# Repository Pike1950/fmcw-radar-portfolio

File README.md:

# 24 GHz FMCW Radar Sensor

A personal engineering portfolio project: a short-range 24 GHz FMCW radar sensor spanning an RF front end, a mixed-signal I/Q baseband, and an FPGA digital backend. It began as a baseband redesign of a Texas Tech senior capstone (HOTRODS, Spring 2020) and has grown into a complete radar sensor design, carried out with the discipline of 4+ years of hardware validation at Texas Instruments.

## Project Overview

This project demonstrates RF integration, mixed-signal PCB design, digital hardware design, hardware verification, and system-level engineering, with first-principles documentation explaining every design decision. The completed work is a corrected, first-principles baseband design and its system design document; the active phase is scaling that foundation into a full 24 GHz radar sensor.

## The System

An FMCW (Frequency-Modulated Continuous Wave) radar transmits a frequency chirp, receives the reflection from a target, and mixes it with the current transmit frequency to produce a low-frequency beat signal. The beat frequency is proportional to range; the chirp-to-chirp phase gives Doppler velocity, and a complex (I/Q) baseband resolves the sign of that velocity (approaching versus receding).

The sensor is built around an integrated 24 GHz transceiver MMIC and is partitioned into two boards plus a downstream digital backend:

```
RF FRONT-END MODULE                       I/Q BASEBAND BOARD                    DIGITAL BACKEND
BGT24MTR11 (24 GHz, 1 TX / 1 RX)          per channel:                          range-Doppler FFT
 on-chip VCO, PA, LNA, I/Q mixers   I,Q   VGA -> anti-alias -> 18-bit SAR ADC    (FPGA / MCU) -> host
 TX/RX antennas, chirp ramp,        --->  I and Q sampled simultaneously
 first gain stage                  (zero  SPI control of the MMIC
                                     IF)
```

The two boards meet at a low-frequency analog I/Q interface, not a 24 GHz one, because the MMIC downconverts on-chip. That seam is what makes the split practical: the costly, iteration-prone 24 GHz RF and antennas stay on a small module, while the baseband stays on inexpensive FR4 and can be brought up and validated on its own.

## Evolution: Rev A to Rev B to Rev C

- **Rev A (2020).** 5.8 GHz, 3 RX channels, 182 components, Eagle, a single flat sheet. Built as the Texas Tech senior capstone; non-functional. The headline defect was a 10 kHz chirp rate that produced only about 5 ADC samples per ramp, far too few for FFT range extraction.
- **Rev B (current).** Began as a scaled, corrected 5.8 GHz baseband (one channel, KiCad 9, a modern signal chain, DFT-first methodology), captured as schematic plus a first-principles system design document. Rather than fabricate that band, Rev B is now redefined as the **24 GHz I/Q radar**: the band moves to 24 GHz, the project adopts the BGT24MTR11 (so it now owns the RF front end, not just the baseband), the baseband goes complex I/Q, and the sensor splits into an RF module and a baseband board. The baseband modernization below carries forward intact.
- **Rev C.** Additional receive channels for angle estimation, the original trilateration goal, on a proven single-channel Rev B.

### Baseband modernization (carried forward from the 5.8 GHz Rev B)

These corrections to the capstone baseband are band-agnostic and carry directly into the 24 GHz I/Q design.

| Aspect | Rev A (2020) | Rev B baseband (carried forward) |
| --- | --- | --- |
| EDA | Eagle 9.5, flat single sheet | KiCad 9, hierarchical |
| VGA | LT6230 + MCP4017 I²C digital pot | PGA113 (SPI, internal gain resistors) |
| ADC | ADS1174 (16-bit, 64-pin QFP, solder bridges) | ADS8881 (18-bit, 10-pin VSSOP) |
| SE to Diff | LTC6242 (improvised, no VOCM) | THS4531A (true FDA with VOCM) |
| Power | Single 3.3 V rail | 3V3A / 3V3D split via ferrite bead |
| Reference | Resistor divider | REF5025 (2.500 V, 0.05%, 3 µVpp) |
| DFT | None | J_DFT header, 17 TPs, 5 MMCX, 6 isolation resistors |

On top of this, the 24 GHz move adds an integrated-MMIC RF front end, a complex I/Q baseband (the chain above duplicated for I and Q with simultaneous sampling), and the two-board partition.

## Key Documents

| Document | Description |
| --- | --- |
| [System Design Document](https://pike1950.github.io/fmcw-radar-portfolio/docs/system-design/System_Design_Document_RevB.html) | The 24 GHz radar system SDD, restyled to the PMVB module-doc schema with PHYSICS / DECISION / TRADEOFF / RISK reasoning callouts. Covers the two-board architecture, the carry-over analog design (power, references, gain, anti-alias filter, DFT), the FMCW principles, and an open decision register tracking the remaining 24 GHz choices. |

## Technical Highlights

### Analog and mixed-signal design

- **Supply splitting via ferrite bead.** BLM18PG221SN1D (220 Ω at 100 MHz) isolates analog from digital supply noise on a single continuous ground plane, with first-principles impedance analysis.
- **Paired decoupling capacitors.** Matched cap pairs (for example 10 µF + 100 nF) with different self-resonant frequencies for low impedance across a wide band, placed per a derived trace-inductance budget.
- **DFT-first methodology.** Test points, MMCX probes, and isolation resistors designed before the signal chain, now applied per channel for I and Q.

### System-level analysis

- **Chirp-rate correction.** Identified the Rev A parameter mismatch (about 5 samples per ramp) and derived the corrected chirp plan from first principles (sample-count-per-ramp to FFT resolution). The analysis is carrier-independent and re-derives the 24 GHz filter and ADC plan.
- **Band move to 24 GHz with complex I/Q.** Moving from 5.8 GHz to the 24 GHz ISM band raises range resolution from about 5 m to about 0.6 m and brings the RF front end into scope through an integrated MMIC. Complex I/Q sampling adds sign-of-velocity discrimination.
- **Designed for validation.** The board is designed for standalone bring-up and characterization on a homebrew SCPI instrument platform (see Related Repositories).

### Digital backend (planned)

SystemVerilog modules targeting the Gowin GW5A (Tang Primer 25K): SPI masters for the ADS8881 and the MMIC, a chirp ramp / DDS generator, a configurable FIR, and a deterministic timing controller, all verified with self-checking Verilator testbenches. See `digital/spi-controller/`.

## Related Repositories

| Repository | Description | Status |
| --- | --- | --- |
| [32-bit RISC Pipelined Processor](https://github.com/Pike1950/BradW_ECE4375_RISC_Pipeline) | 4-stage pipelined CPU refactored from Verilog to SystemVerilog. Shares the Verilator-clean SystemVerilog methodology used for this radar's digital backend. | SV conversion complete, synthesis next |
| [Poor Man's Validation Bench](https://github.com/Pike1950/poor-mans-validation-bench) | Modular SCPI + MCP instrument platform: Raspberry Pi 5 orchestration, Pico 2W USB-TMC modules, tiered FPGA. The bring-up and characterization platform for this radar. | Phase 0 complete; Module 1E (AWG) in build |

## Tools and Technologies

- **EDA:** KiCad 9. RF module on a controlled high-frequency stackup; baseband on FR4.
- **Simulation:** LTspice (analog), Verilator (digital), GTKWave (waveforms).
- **HDL:** SystemVerilog (digital backend, verification).
- **FPGA target:** Gowin GW5A (Sipeed Tang Primer 25K) for the digital backend.
- **Documentation:** Markdown rendered to HTML via Pandoc, PMVB-schema design docs with first-principles reasoning callouts.
- **Test automation:** PyVISA, integrating with the Poor Man's Validation Bench.

## Background

This project is one of four interconnected portfolio tracks:

1. **FMCW Radar Sensor** (this repo). RF integration plus mixed-signal PCB plus digital, with first-principles documentation and DFT-first methodology.
2. **Hardware Validation.** 4+ years at Texas Instruments (gate-driver characterization, automated test with LabVIEW / TestStand / PXI, DUT board design in Altium).
3. **Digital Design.** A pipelined RISC processor in SystemVerilog.
4. **Test Infrastructure.** The Poor Man's Validation Bench, a SCPI + MCP instrument platform.

The radar connects all four: a mixed-signal and RF sensor (track 1), designed with validation-engineer discipline (track 2), with an FPGA backend (track 3) characterized on the homebrew bench (track 4).

## Status

- **5.8 GHz baseband foundation (complete).** First-principles system design document and schematic capture of the corrected single-channel baseband. Established the methodology, the analog signal chain, and the DFT infrastructure that all carry forward.
- **24 GHz radar system design (in progress).**
  - System SDD reframed to the radar scope and the PMVB schema.
  - D1 resolved: BGT24MTR11 (1 TX / 1 RX), two-board partition (RF Front-End Module plus I/Q Baseband Board).
  - Open: antenna and RF stackup, ADC arrangement, ramp generation, chirp plan, and digital backend (tracked in the SDD decision register).
- **Next.** RF Front-End Module and I/Q Baseband Board schematics; digital backend RTL; bring-up and characterization on the Poor Man's Validation Bench.

## License

A personal engineering portfolio project. The FMCW radar originated as a Texas Tech senior capstone (HOTRODS, Spring 2020). The Rev B redesign, the 24 GHz radar system design, documentation, and all digital design work are by Bradley Ward.

## Contact

Bradley Ward, bradw858@gmail.com, [LinkedIn](https://linkedin.com/in/bradley-ward-49087766/)

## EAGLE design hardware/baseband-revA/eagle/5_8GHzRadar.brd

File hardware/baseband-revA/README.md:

# Baseband Rev A — Eagle 9.5 (Original Senior Capstone)

## Overview

Original 3-channel FMCW radar baseband designed for the HOTRODS senior capstone project at Texas Tech University (Spring 2020). This design is preserved for reference — it shows what was built originally and documents the failures that motivated the Rev B redesign.

## Architecture

- **3 identical RX channels**, each with: LT6230 VGA + MCP4017 I²C digital pot → 4th-order Sallen-Key LP (LTC6242, 25 kHz cutoff) → SE-to-Diff converter (LTC6242, remaining 2 amps)
- **On-board ADC:** ADS1174IPAPT (quad 16-bit, 52 kSPS, 64-pin TQFP)
- **Power:** NCP163ASN330T1G 3.3V LDO, single rail, no analog/digital splitting
- **182 total components** on a single flat Eagle sheet

## What Went Wrong

1. **ADS1174 solder bridges** — 64-pin QFP with sub-mm pitch; pins bridged during hand assembly
2. **TPS717185 (1.8V LDO) solder bridges** — same issue
3. **No test infrastructure** — zero test points, no DFT header, no isolation capability
4. **Power routing error** — power connected through RX_3 section only; RX_1 required wire jumpers
5. **COVID-19 shutdown** — prevented further debugging after initial partial success

## Files

- `5_8GHzRadar.sch` — Eagle 9.5 schematic (all 3 channels + power on one sheet)
- `5_8GHzRadar.brd` — Eagle 9.5 board layout (4-layer, OSHPark)

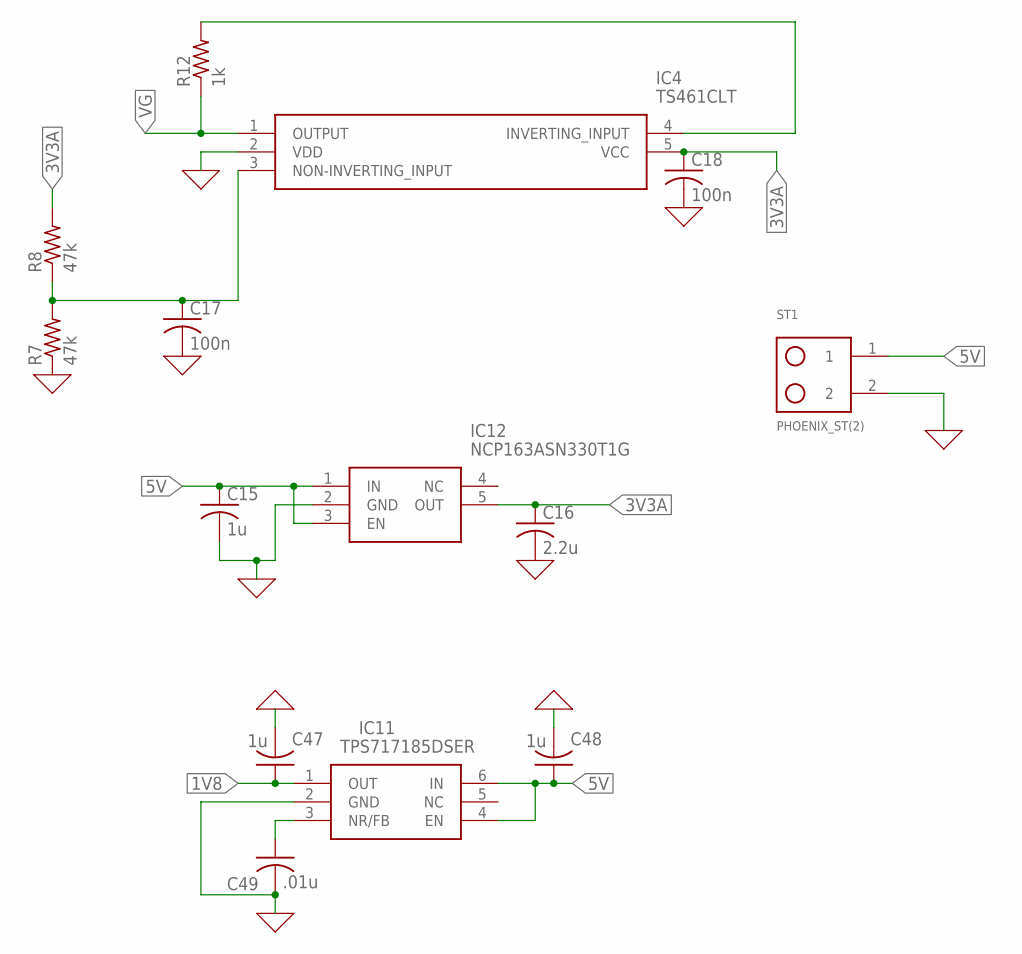
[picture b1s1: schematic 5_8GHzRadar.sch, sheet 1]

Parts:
C15, C47, C48: 1u; C0805
C16: 2.2u; C0805
C17, C18: 100n; C0805
C49: .01u; C0805
IC4: TS461CLT; SOT95P280X145-5N@1
IC11: TPS717185DSER; SON50P150X150X80-6N
IC12: NCP163ASN330T1G; SOT95P280X145-5N
R7, R8: 47k; R0805
R12: 1k; R0805
ST1: PHOENIX_ST(2); PHEONIX_SCREW(2)

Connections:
0: C15.2, C16.2, C17.2, C18.2, C47.2, C48.2, C49.2, IC4.2 (VDD), IC11.2 (GND), IC12.2 (GND), R7.1, ST1.2; also elsewhere on the board
1V8: C47.1, IC11.1 (OUT); also elsewhere on the board
3V3A: C16.1, C18.1, IC4.5 (VCC), IC12.5 (OUT), R8.2; also elsewhere on the board
5V: C15.1, C48.1, IC11.4 (EN), IC11.6 (IN), IC12.1 (IN), IC12.3 (EN), ST1.1; also elsewhere on the board
unnamed: C17.1, IC4.3 (NON-INVERTING_INPUT), R7.2, R8.1
unnamed: IC4.4 (INVERTING_INPUT), R12.2
unnamed: C49.1, IC11.3 (NR/FB)
VG: IC4.1 (OUTPUT), R12.1; also elsewhere on the board

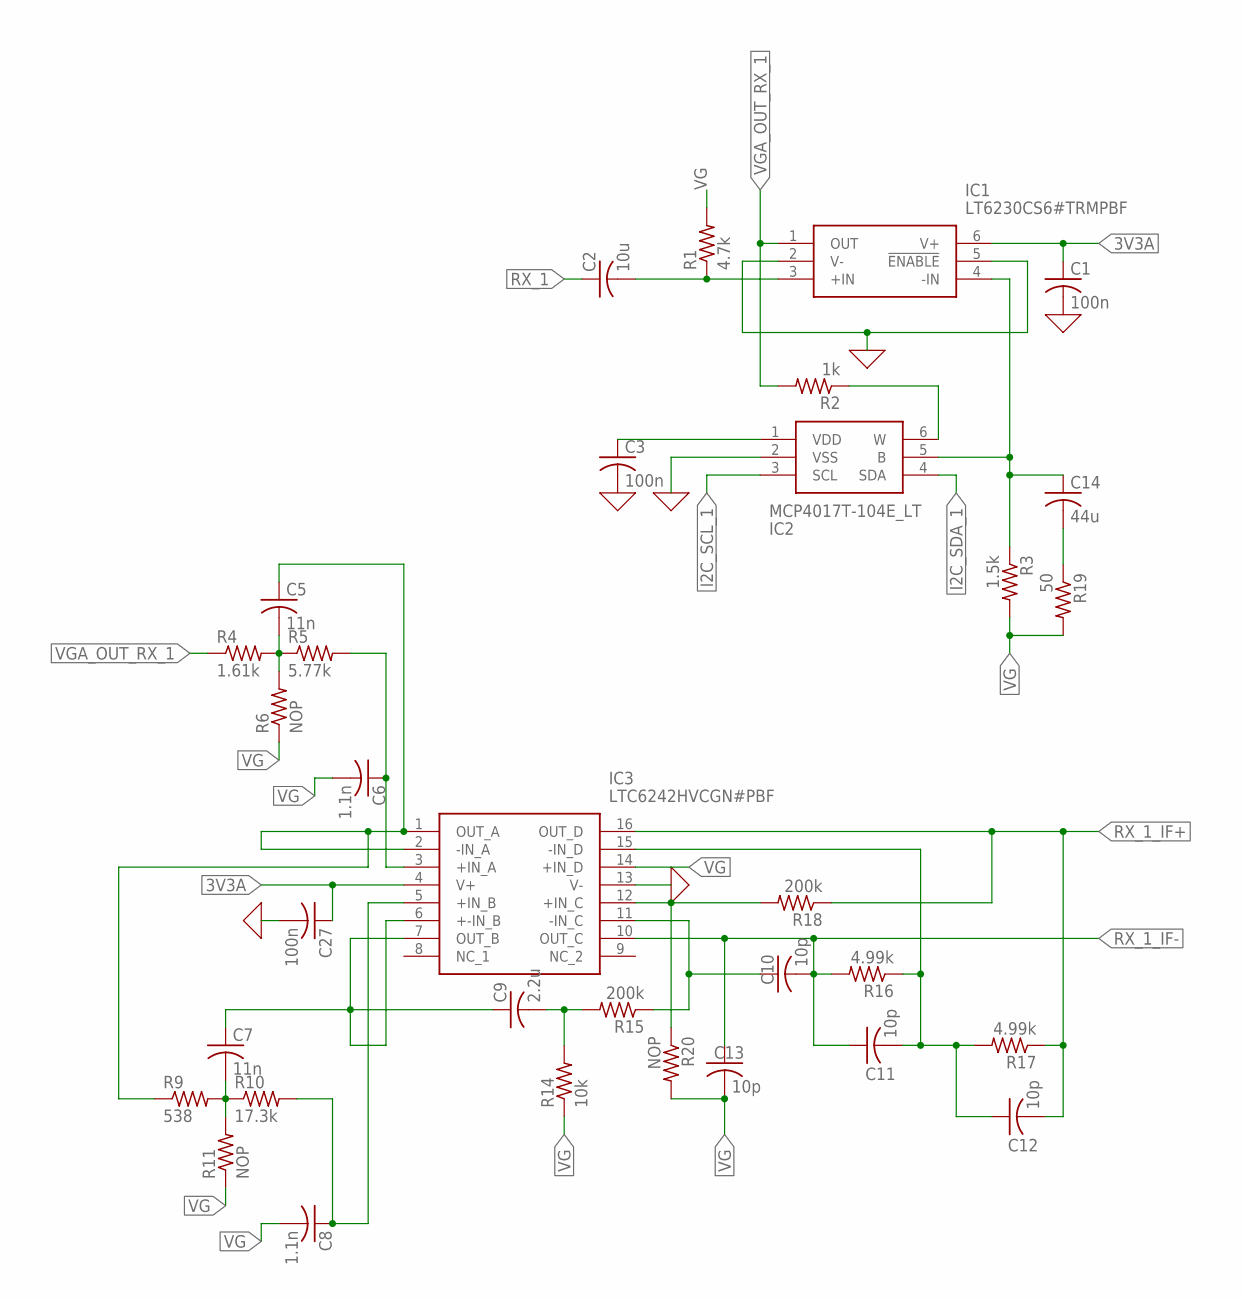
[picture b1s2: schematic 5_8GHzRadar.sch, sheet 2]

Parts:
C1, C3, C27: 100n; C0805
C2: 10u; C0805
C5, C7: 11n; C0805
C6, C8: 1.1n; C0805
C9: 2.2u; C0805
C10, C11, C12, C13: 10p; C0805
C14: 44u; C0603
IC1: LT6230CS6#TRMPBF; SOT95P280X100-6N
IC2: MCP4017T-104E_LT; SOT65P210X110-6N
IC3: LTC6242HVCGN#PBF; SOP64P601X175-16N
R1: 4.7k; R0805
R2: 1k; R0805
R3: 1.5k; R0805
R4: 1.61k; R0805
R5: 5.77k; R0805
R6, R11, R20: NOP; R0805
R9: 538; R0805
R10: 17.3k; R0805
R14: 10k; R0805
R15, R18: 200k; R0805
R16, R17: 4.99k; R0805
R19: 50; R0805

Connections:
0: C1.2, C3.2, C27.2, IC1.2 (V-), IC1.5 (!ENABLE), IC2.2 (VSS), IC3.13 (V-); also elsewhere on the board
3V3A: C1.1, C27.1, IC1.6 (V+), IC3.4 (V+); also elsewhere on the board
FILTER1: C5.1, IC3.1 (OUT_A), IC3.2 (-IN_A), R9.1
I2C_SCL_1: IC2.3 (SCL); also elsewhere on the board
I2C_SDA_1: IC2.4 (SDA); also elsewhere on the board
unnamed: C14.1, IC1.4 (-IN), IC2.5 (B), R3.1
unnamed: C2.2, IC1.3 (+IN), R1.1
unnamed: C5.2, R4.2, R5.1, R6.2
unnamed: IC2.6 (W), R2.1
unnamed: C3.1, IC2.1 (VDD)
unnamed: C9.2, R14.2, R15.2
unnamed: C6.1, IC3.3 (+IN_A), R5.2
unnamed: C7.2, R9.2, R10.1, R11.2
unnamed: C8.1, IC3.5 (+IN_B), R10.2
unnamed: C7.1, C9.1, IC3.6 (+-IN_B), IC3.7 (OUT_B)
unnamed: C10.1, IC3.11 (-IN_C), R15.1
unnamed: C14.2, R19.1
unnamed: IC3.12 (+IN_C), R18.2, R20.1
unnamed: C11.2, C12.1, IC3.15 (-IN_D), R16.1, R17.2
RX_1: C2.1; also elsewhere on the board
RX_1_IF+: C12.2, IC3.16 (OUT_D), R17.1, R18.1; also elsewhere on the board
RX_1_IF-: C10.2, C11.1, C13.1, IC3.10 (OUT_C), R16.2; also elsewhere on the board
VG: C6.2, C8.2, C13.2, IC3.14 (+IN_D), R1.2, R3.2, R6.1, R11.1, R14.1, R19.2, R20.2; also elsewhere on the board
VGA_OUT_RX_1: IC1.1 (OUT), R2.2, R4.1

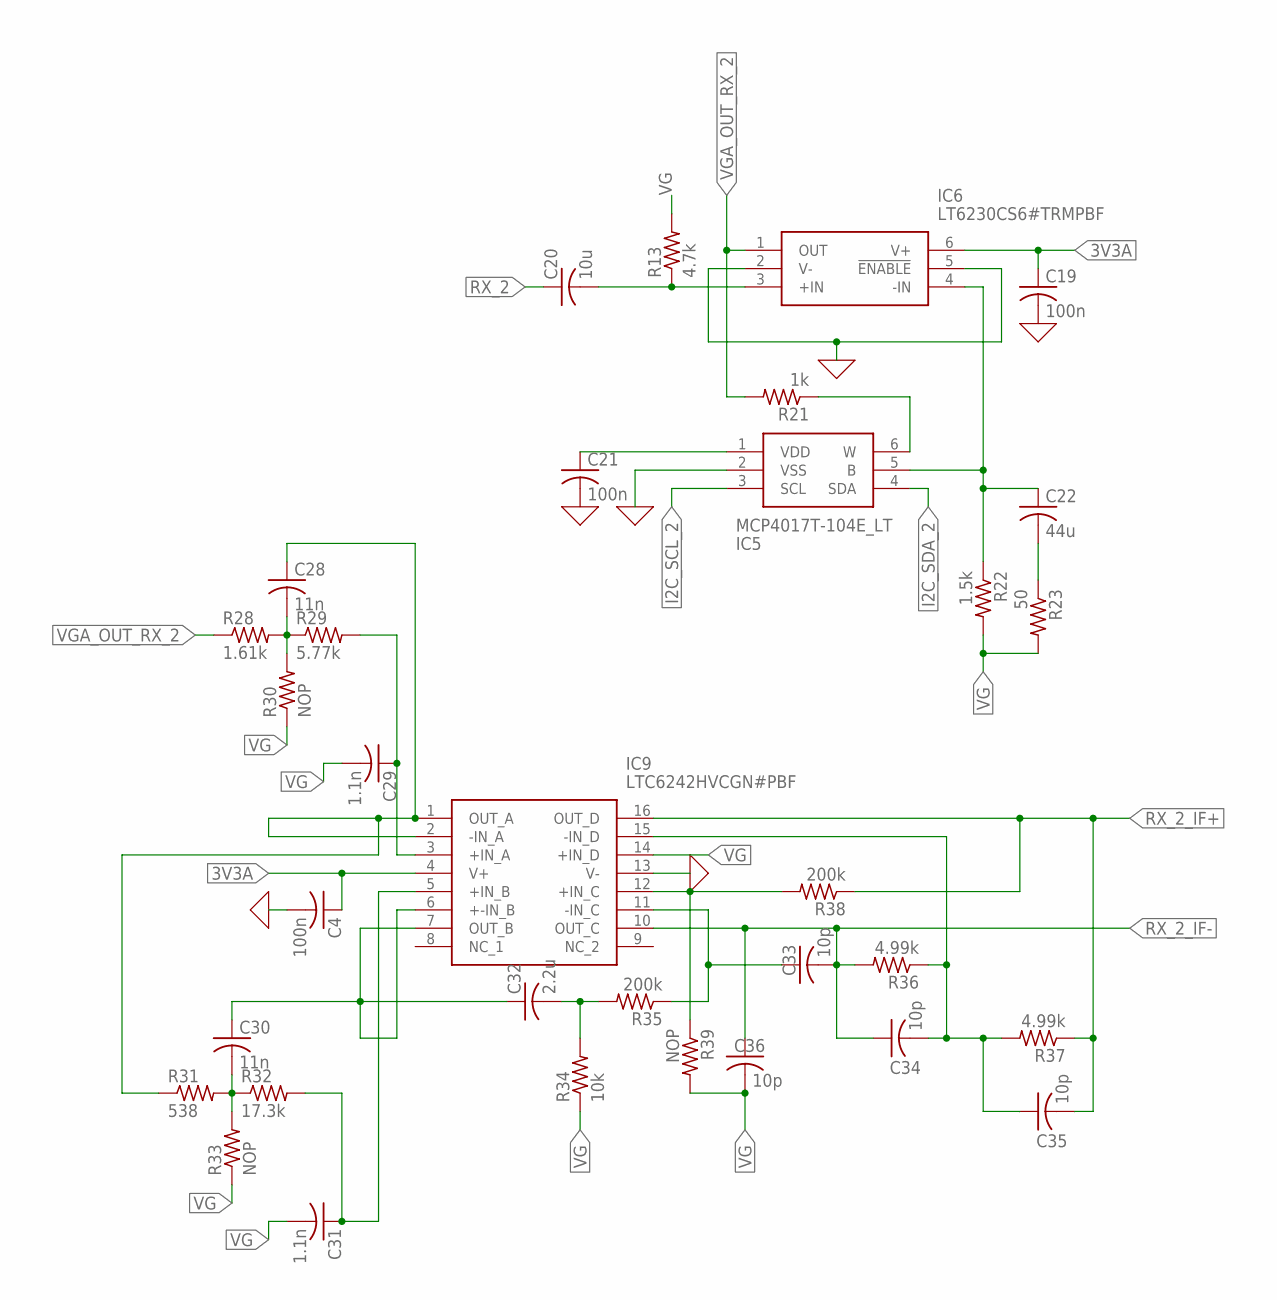
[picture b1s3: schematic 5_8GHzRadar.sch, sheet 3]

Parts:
C4, C19, C21: 100n; C0805
C20: 10u; C0805
C22: 44u; C0805
C28, C30: 11n; C0805
C29, C31: 1.1n; C0805
C32: 2.2u; C0805
C33, C34, C35, C36: 10p; C0805
IC5: MCP4017T-104E_LT; SOT65P210X110-6N
IC6: LT6230CS6#TRMPBF; SOT95P280X100-6N
IC9: LTC6242HVCGN#PBF; SOP64P601X175-16N
R13: 4.7k; R0805
R21: 1k; R0805
R22: 1.5k; R0805
R23: 50; R0805
R28: 1.61k; R0805
R29: 5.77k; R0805
R30, R33, R39: NOP; R0805
R31: 538; R0805
R32: 17.3k; R0805
R34: 10k; R0805
R35, R38: 200k; R0805
R36, R37: 4.99k; R0805

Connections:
0: C4.2, C19.2, C21.2, IC5.2 (VSS), IC6.2 (V-), IC6.5 (!ENABLE), IC9.13 (V-); also elsewhere on the board
3V3A: C4.1, C19.1, IC6.6 (V+), IC9.4 (V+); also elsewhere on the board
FILTER2: C28.1, IC9.1 (OUT_A), IC9.2 (-IN_A), R31.1
I2C_SCL_2: IC5.3 (SCL); also elsewhere on the board
I2C_SDA_2: IC5.4 (SDA); also elsewhere on the board
unnamed: C22.1, IC5.5 (B), IC6.4 (-IN), R22.1
unnamed: C20.2, IC6.3 (+IN), R13.1
unnamed: IC5.6 (W), R21.1
unnamed: C21.1, IC5.1 (VDD)
unnamed: C22.2, R23.1
unnamed: C28.2, R28.2, R29.1, R30.2
unnamed: C29.1, IC9.3 (+IN_A), R29.2
unnamed: C30.2, R31.2, R32.1, R33.2
unnamed: C31.1, IC9.5 (+IN_B), R32.2
unnamed: C30.1, C32.1, IC9.6 (+-IN_B), IC9.7 (OUT_B)
unnamed: C32.2, R34.2, R35.2
unnamed: C33.1, IC9.11 (-IN_C), R35.1
unnamed: C34.2, C35.1, IC9.15 (-IN_D), R36.1, R37.2
unnamed: IC9.12 (+IN_C), R38.2, R39.1
RX_2: C20.1; also elsewhere on the board
RX_2_IF+: C35.2, IC9.16 (OUT_D), R37.1, R38.1; also elsewhere on the board
RX_2_IF-: C33.2, C34.1, C36.1, IC9.10 (OUT_C), R36.2; also elsewhere on the board
VG: C29.2, C31.2, C36.2, IC9.14 (+IN_D), R13.2, R22.2, R23.2, R30.1, R33.1, R34.1, R39.2; also elsewhere on the board
VGA_OUT_RX_2: IC6.1 (OUT), R21.2, R28.1

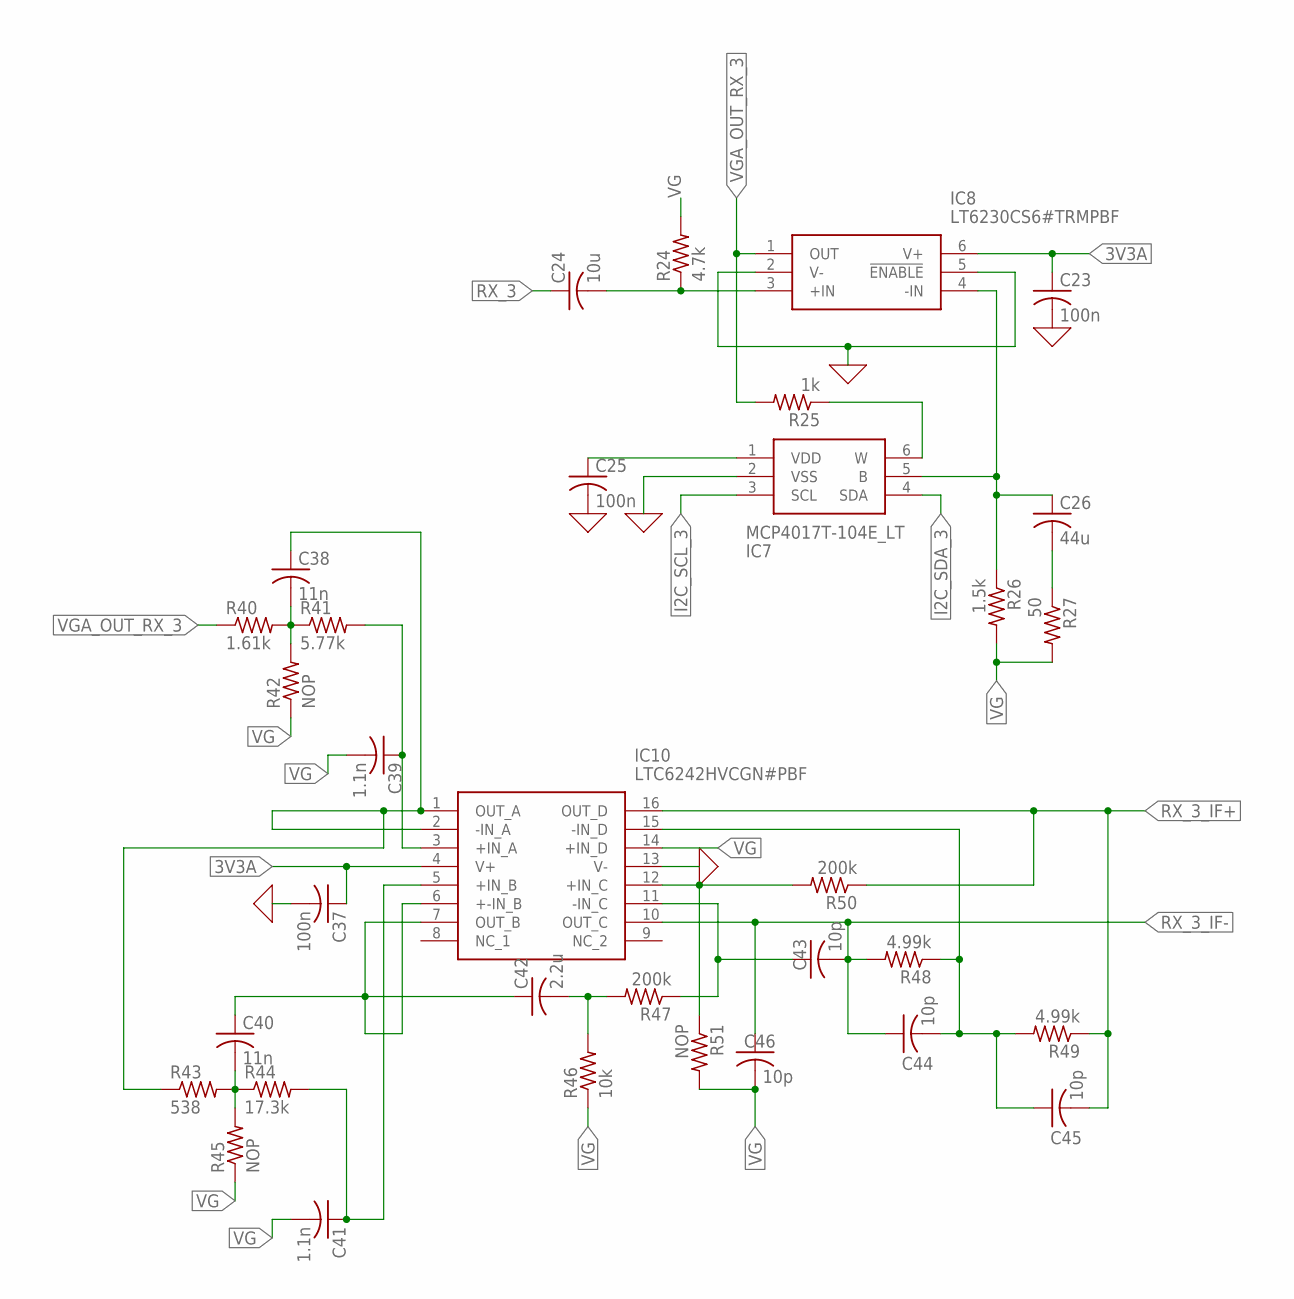
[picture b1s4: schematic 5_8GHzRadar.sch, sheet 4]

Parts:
C23, C25, C37: 100n; C0805
C24: 10u; C0805
C26: 44u; C0805
C38, C40: 11n; C0805
C39, C41: 1.1n; C0805
C42: 2.2u; C0805
C43, C44, C45, C46: 10p; C0805
IC7: MCP4017T-104E_LT; SOT65P210X110-6N
IC8: LT6230CS6#TRMPBF; SOT95P280X100-6N
IC10: LTC6242HVCGN#PBF; SOP64P601X175-16N
R24: 4.7k; R0805
R25: 1k; R0805
R26: 1.5k; R0805
R27: 50; R0805
R40: 1.61k; R0805
R41: 5.77k; R0805
R42, R45, R51: NOP; R0805
R43: 538; R0805
R44: 17.3k; R0805
R46: 10k; R0805
R47, R50: 200k; R0805
R48, R49: 4.99k; R0805

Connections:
0: C23.2, C25.2, C37.2, IC7.2 (VSS), IC8.2 (V-), IC8.5 (!ENABLE), IC10.13 (V-); also elsewhere on the board
3V3A: C23.1, C37.1, IC8.6 (V+), IC10.4 (V+); also elsewhere on the board
FILTER3: C38.1, IC10.1 (OUT_A), IC10.2 (-IN_A), R43.1
I2C_SCL_3: IC7.3 (SCL); also elsewhere on the board
I2C_SDA_3: IC7.4 (SDA); also elsewhere on the board
unnamed: C26.1, IC7.5 (B), IC8.4 (-IN), R26.1
unnamed: C24.2, IC8.3 (+IN), R24.1
unnamed: IC7.6 (W), R25.1
unnamed: C25.1, IC7.1 (VDD)
unnamed: C26.2, R27.1
unnamed: C38.2, R40.2, R41.1, R42.2
unnamed: C39.1, IC10.3 (+IN_A), R41.2
unnamed: C40.2, R43.2, R44.1, R45.2
unnamed: C41.1, IC10.5 (+IN_B), R44.2
unnamed: C40.1, C42.1, IC10.6 (+-IN_B), IC10.7 (OUT_B)
unnamed: C42.2, R46.2, R47.2
unnamed: C43.1, IC10.11 (-IN_C), R47.1
unnamed: C44.2, C45.1, IC10.15 (-IN_D), R48.1, R49.2
unnamed: IC10.12 (+IN_C), R50.2, R51.1
RX_3: C24.1; also elsewhere on the board
RX_3_IF+: C45.2, IC10.16 (OUT_D), R49.1, R50.1; also elsewhere on the board
RX_3_IF-: C43.2, C44.1, C46.1, IC10.10 (OUT_C), R48.2; also elsewhere on the board
VG: C39.2, C41.2, C46.2, IC10.14 (+IN_D), R24.2, R26.2, R27.2, R42.1, R45.1, R46.1, R51.2; also elsewhere on the board
VGA_OUT_RX_3: IC8.1 (OUT), R25.2, R40.1

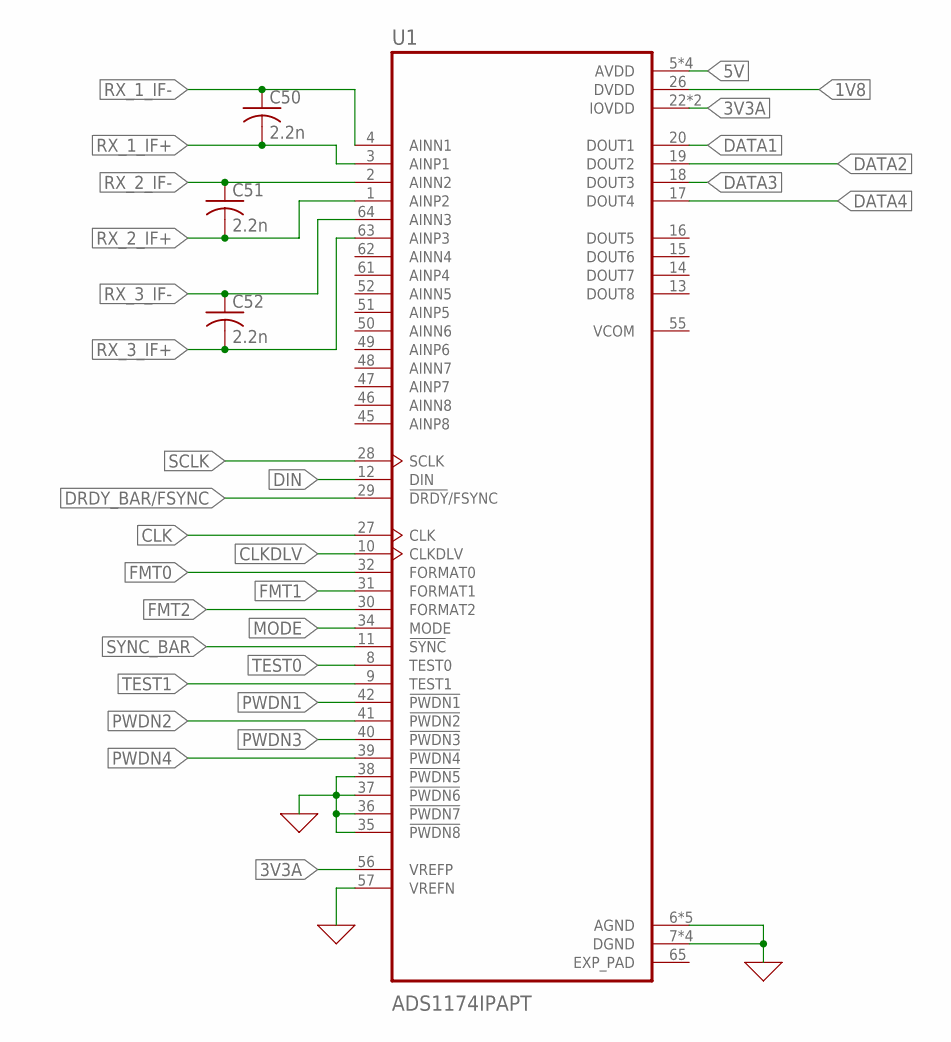
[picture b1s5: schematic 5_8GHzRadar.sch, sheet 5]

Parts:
C50, C51, C52: 2.2n; C0805
U1: ADS1174IPAPT; QFP50P1200X1200X120-65N

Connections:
0: U1.6 (AGND), U1.7 (DGND), U1.21 (DGND), U1.24 (DGND), U1.25 (DGND), U1.35 (!PWDN8), U1.36 (!PWDN7), U1.37 (!PWDN6), U1.38 (!PWDN5), U1.43 (AGND), U1.54 (AGND), U1.57 (VREFN), U1.58 (AGND), U1.59 (AGND); also elsewhere on the board
1V8: U1.26 (DVDD); also elsewhere on the board
3V3A: U1.22 (IOVDD), U1.23 (IOVDD), U1.56 (VREFP); also elsewhere on the board
5V: U1.5 (AVDD), U1.44 (AVDD), U1.53 (AVDD), U1.60 (AVDD); also elsewhere on the board
CLK: U1.27 (CLK); also elsewhere on the board
CLKDLV: U1.10 (CLKDLV); also elsewhere on the board
DATA1: U1.20 (DOUT1); also elsewhere on the board
DATA2: U1.19 (DOUT2); also elsewhere on the board
DATA3: U1.18 (DOUT3); also elsewhere on the board
DATA4: U1.17 (DOUT4); also elsewhere on the board
DIN: U1.12 (DIN); also elsewhere on the board
DRDY_BAR/FSYNC: U1.29 (!DRDY!/FSYNC); also elsewhere on the board
EXP_PAD: U1.65 (EXP_PAD)
FMT0: U1.32 (FORMAT0); also elsewhere on the board
FMT1: U1.31 (FORMAT1); also elsewhere on the board
FMT2: U1.30 (FORMAT2); also elsewhere on the board
MODE: U1.34 (MODE); also elsewhere on the board
PWDN1: U1.42 (!PWDN1); also elsewhere on the board
PWDN2: U1.41 (!PWDN2); also elsewhere on the board
PWDN3: U1.40 (!PWDN3); also elsewhere on the board
PWDN4: U1.39 (!PWDN4); also elsewhere on the board
RX_1_IF+: C50.2, U1.3 (AINP1); also elsewhere on the board
RX_1_IF-: C50.1, U1.4 (AINN1); also elsewhere on the board
RX_2_IF+: C51.2, U1.1 (AINP2); also elsewhere on the board
RX_2_IF-: C51.1, U1.2 (AINN2); also elsewhere on the board
RX_3_IF+: C52.2, U1.63 (AINP3); also elsewhere on the board
RX_3_IF-: C52.1, U1.64 (AINN3); also elsewhere on the board
SCLK: U1.28 (SCLK); also elsewhere on the board
SYNC_BAR: U1.11 (!SYNC); also elsewhere on the board
TEST0: U1.8 (TEST0); also elsewhere on the board
TEST1: U1.9 (TEST1); also elsewhere on the board

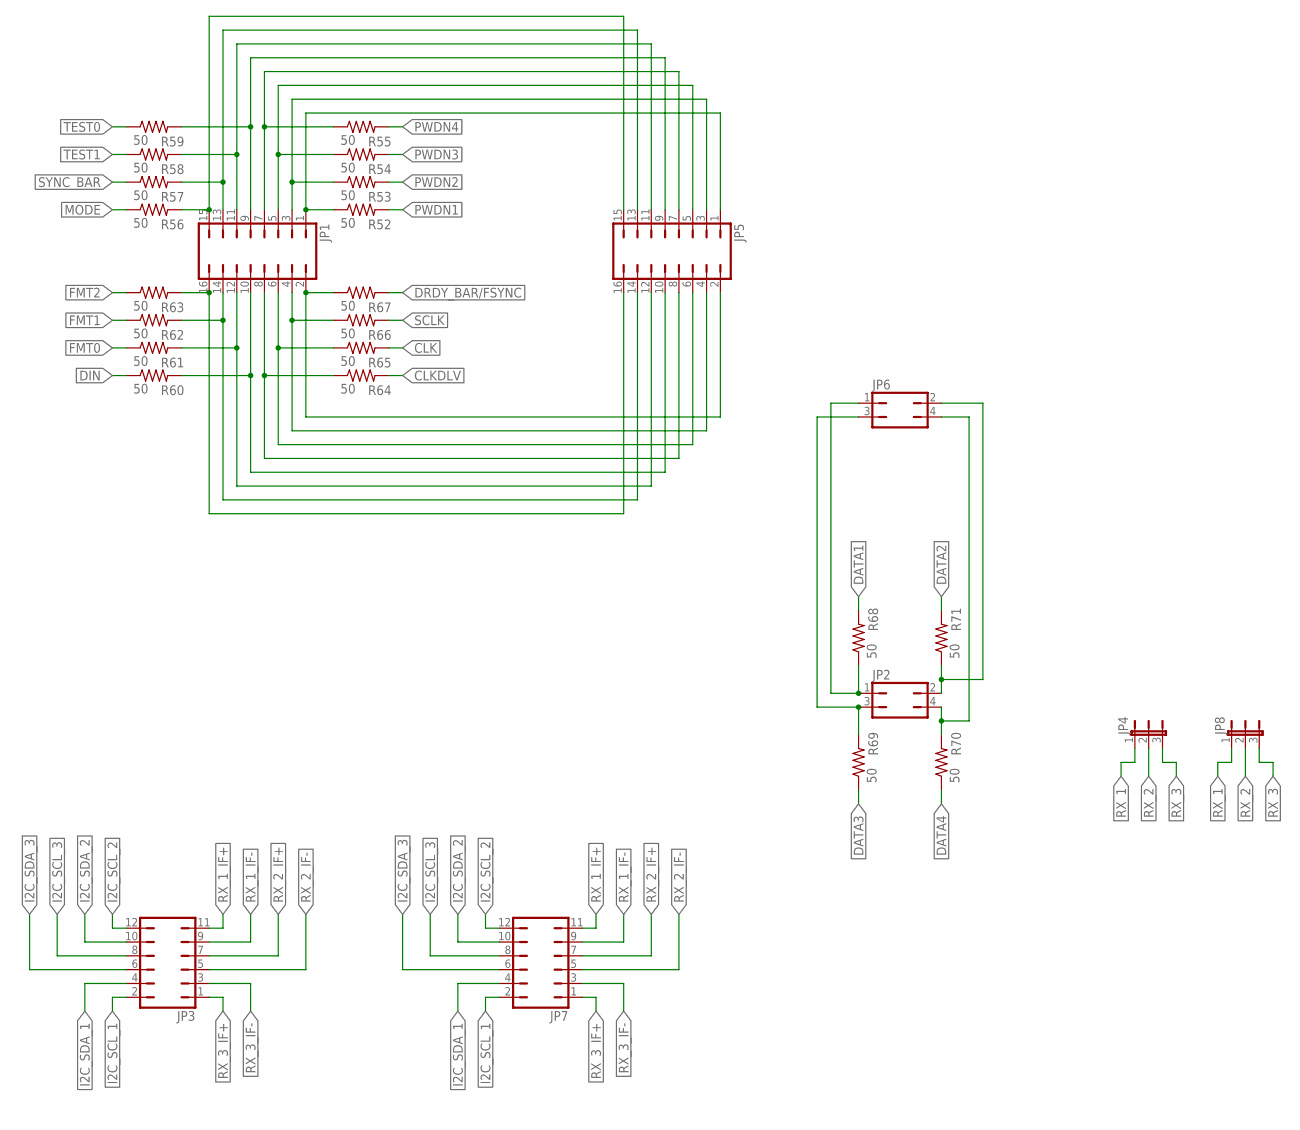
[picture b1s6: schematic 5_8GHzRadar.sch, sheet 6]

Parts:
JP1, JP5: JP8Q
JP2, JP6: JP2Q
JP3, JP7: JP6Q
JP4, JP8: JP2E; JP2
R52, R53, R54, R55, R56, R57, R58, R59, R60, R61, R62, R63, R64, R65, R66, R67, R68, R69, R70, R71: 50; R0805

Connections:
CLK: R65.2; also elsewhere on the board
CLKDLV: R64.2; also elsewhere on the board
DATA1: R68.2; also elsewhere on the board
DATA2: R71.2; also elsewhere on the board
DATA3: R69.1; also elsewhere on the board
DATA4: R70.1; also elsewhere on the board
DIN: R60.1; also elsewhere on the board
DRDY_BAR/FSYNC: R67.2; also elsewhere on the board
FMT0: R61.1; also elsewhere on the board
FMT1: R62.1; also elsewhere on the board
FMT2: R63.1; also elsewhere on the board
I2C_SCL_1: JP3.2, JP7.2; also elsewhere on the board
I2C_SCL_2: JP3.12, JP7.12; also elsewhere on the board
I2C_SCL_3: JP3.8, JP7.8; also elsewhere on the board
I2C_SDA_1: JP3.4, JP7.4; also elsewhere on the board
I2C_SDA_2: JP3.10, JP7.10; also elsewhere on the board
I2C_SDA_3: JP3.6, JP7.6; also elsewhere on the board
MODE: R56.1; also elsewhere on the board
unnamed: JP1.1, JP5.1, R52.1
unnamed: JP1.3, JP5.3, R53.1
unnamed: JP1.5, JP5.5, R54.1
unnamed: JP1.7, JP5.7, R55.1
unnamed: JP1.9, JP5.9, R59.2
unnamed: JP1.15, JP5.15, R56.2
unnamed: JP1.13, JP5.13, R57.2
unnamed: JP1.11, JP5.11, R58.2
unnamed: JP1.16, JP5.16, R63.2
unnamed: JP1.10, JP5.10, R60.2
unnamed: JP1.12, JP5.12, R61.2
unnamed: JP1.14, JP5.14, R62.2
unnamed: JP1.8, JP5.8, R64.1
unnamed: JP1.6, JP5.6, R65.1
unnamed: JP1.4, JP5.4, R66.1
unnamed: JP1.2, JP5.2, R67.1
unnamed: JP2.1, JP6.1, R68.1
unnamed: JP2.3, JP6.3, R69.2
unnamed: JP2.4, JP6.4, R70.2
unnamed: JP2.2, JP6.2, R71.1
PWDN1: R52.2; also elsewhere on the board
PWDN2: R53.2; also elsewhere on the board
PWDN3: R54.2; also elsewhere on the board
PWDN4: R55.2; also elsewhere on the board
RX_1: JP4.1, JP8.1; also elsewhere on the board
RX_1_IF+: JP3.11, JP7.11; also elsewhere on the board
RX_1_IF-: JP3.9, JP7.9; also elsewhere on the board
RX_2: JP4.2, JP8.2; also elsewhere on the board
RX_2_IF+: JP3.7, JP7.7; also elsewhere on the board
RX_2_IF-: JP3.5, JP7.5; also elsewhere on the board
RX_3: JP4.3, JP8.3; also elsewhere on the board
RX_3_IF+: JP3.1, JP7.1; also elsewhere on the board
RX_3_IF-: JP3.3, JP7.3; also elsewhere on the board
SCLK: R66.2; also elsewhere on the board
SYNC_BAR: R57.1; also elsewhere on the board
TEST0: R59.1; also elsewhere on the board
TEST1: R58.1; also elsewhere on the board

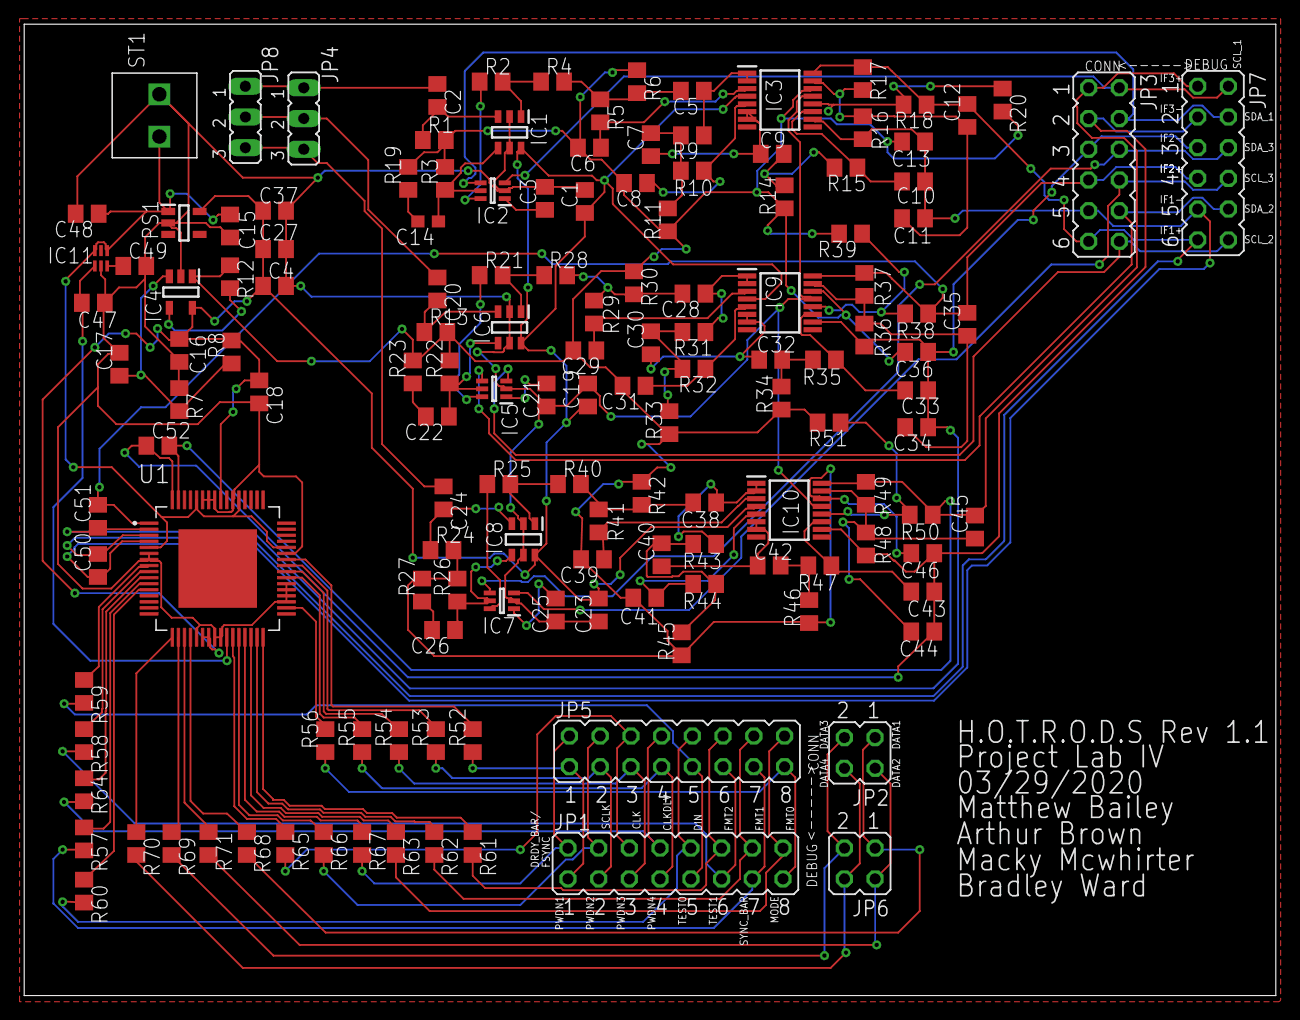
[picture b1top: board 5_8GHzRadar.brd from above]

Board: 2 copper layers, 103.5 x 80.3 mm, 145 parts (0 on the bottom side), 111 nets.

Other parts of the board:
PS1: TPS70918DBVT; SOT95P280X145-5N

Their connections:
0: PS1.2; also elsewhere on the board
3V3A: PS1.5; also elsewhere on the board
5V: PS1.1; also elsewhere on the board

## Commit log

2026-03-25 Initial commit: FMCW radar baseband Rev B schematic and documentation
2026-03-27 Update document links to GitHub Pages URLs
2026-03-27 Remove Project_Evolution.html (contains third-party personal information)
2026-03-27 Remove Project_Evolution (contains third-party personal info), update README
2026-03-27 Fix block diagram SVGs: orthogonal routing, spacing fixes, table CSS for s11
2026-03-27 Complete SVG rebuild: all lines, no paths or polygons, no closed loops
2026-03-27 Update FPGA targets: Tang Nano 9K for radar, Tang Primer 25K in hand for RISC, Phase 2 high-speed boards
2026-03-27 Update FPGA targets: Tang Primer 25K (Phase 1, in hand) and Tang Mega 138K Pro (Phase 2)
2026-03-27 Complete design rationale: add §4 Sheet B, §5 Sheet C, §6 Sheet D - §4: ESD protection, AC coupling (f_HP=33.9Hz), DC bias (47k to VCM) - §5: PGA113 variable gain (1-200x), 4th-order Sallen-Key Butte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
2026-03-27 Add user-adjustable width slider to design rationale (800-2000px)
2026-03-27 Set default width to 2000px and add width slider to all HTML documents
2026-03-27 Rename to System Design Document, remove em-dashes from body text
    - Rename docs/design-rationale/ to docs/system-design/
    - RevB_Design_Rationale.html -> System_Design_Document.html
    - Update title, subtitle, and README links
    - Replace 203 em-dashes in body paragraphs with spaced hyphens
    - Impedance curve SVG generated (integration in next session)
2026-03-27 Add §3.1.3 capacitor placement analysis with trace impedance chart
    - Derive placement rules from trace inductance (1 nH/mm) vs cap impedance
    - SVG impedance chart: 100nF at 1mm/2mm/5mm/10mm trace lengths
    - Worked example: 10mm trace adds 3.3 ohm at 50 MHz (100x cap impedance)
    - Placement rules table: 100nF ≤2mm, 1uF ≤5mm, 10uF ≤10mm
    - Interview-ready summary for capacitor placement rationale
2026-03-27 Add TOC subsections for §4/§5/§6, add §7 placeholder header
2026-03-27 Add collapsible TOC and Table of Figures/Tables, responsive impedance SVG
    - TOC: collapsible overall, each section (§1-§6) independently collapsible
    - Table of Figures & Tables: 5 figures, 21 tables, starts collapsed
    - Impedance diagram: responsive width, centers in container
2026-03-27 Add captions under all 38 tables and 6 figures with anchor IDs
    - Italic caption text below every table and figure in the document
    - Unique anchor IDs (tbl-1-2, fig-3-1, etc.) for direct linking
    - Table of Figures/Tables links updated to jump to specific elements
2026-03-27 Clean up ToF: remove subtitle lines, center table captions
2026-03-27 Add missing figure/table captions: §1.6 radar path, §2.2a signal flow, §3.1 power chain
    - 9 figures and 38 tables now captioned with centered italic labels
    - Table of Figures updated to 8 entries with correct anchor links
    - Fixed duplicate table caption on §2.2 component map
2026-03-27 Integrate all block diagrams into system design document
    - Fig 2.2b: top-level 4-sheet hierarchy with inter-sheet signal routing
    - Fig 3.1b: Sheet A detailed power/reference block diagram
    - Fig 4.1b: Sheet B component-level signal path diagram
    - Fig 6.1b: Sheet D FDA/ADC/J_DFT block diagram with SPI routing
    - Fig 5.1b: Sheet C block diagram (already integrated last commit)
    - Table of Figures updated to 14 entries
2026-03-28 Add schematic and PCB layout change plans, consolidate README status
    - Schematic_Updates_Change_Plan.docx: 9 CRs (SCH-01 to SCH-09)
    Filter wiring fixes, ERC resolution, FPGA connector, schematic freeze
    - PCB_Layout_Change_Plan.docx: 8 tasks (PCB-01 to PCB-08)
    4-layer stackup, placement, ground strategy, routing, DRC
    - README status: consolidated design rationale into single checkbox
    with sub-items, added sub-checkboxes for all SCH and PCB tasks
2026-03-28 Update README with task progress and schematic updates
    Removed completed tasks and updated schematic change plan.
2026-03-28 Schematic audit: correct C14 floating (not grounded), add SCH-00 prerequisite
    Programmatic audit of KiCad schematic found:
    - Zero GND power symbols on Sheet C (new SCH-00 prerequisite)
    - C14 is FLOATING, not grounded as originally reported
    - 7 isolated net labels (placed but not connected to any wire)
    - LTC6242 signal pins entirely unreachable from wire network
    - PGA113 wiring is correct; Sheets A, B, D substantially complete
2026-03-28 Add KiCad SVG schematic exports for all sheets and annotated audit
    - Root_Hierarchy.svg: top-level sheet hierarchy
    - Sheet_A_Power_Refs.svg: power and references
    - Sheet_B_IF_Input.svg: IF input, protection, bias
    - Sheet_C_PGA_Filter.svg: PGA and anti-alias filter
    - Sheet_D_FDA_ADC_SPI.svg: FDA, ADC, SPI interface
    - Sheet_C_Annotated_Audit.svg: Sheet C with issue annotations
2026-03-28 Add KiCad schematic SVG exports and updated annotated audit
    - Root_Hierarchy.svg: top-level hierarchical sheet view
    - Sheet_A_Power_Refs.svg: power rail and reference generation
    - Sheet_B_IF_Input.svg: IF input with ESD, AC coupling, DC bias
    - Sheet_C_PGA_Filter.svg: PGA113 and Sallen-Key filter (pre-fix)
    - Sheet_D_FDA_ADC_SPI.svg: THS4531A FDA, ADS8881 ADC, SPI/DFT
    - Sheet_C_Annotated_Audit.svg: color-coded audit overlay
2026-03-28 Rename KiCad SVG exports and integrate into SDD
    Schematic exports renamed from KiCad defaults to clean names:
    - Baseband PCB.svg → Root_Hierarchy.svg
    - Baseband PCB-Baseband_Power_Refs.svg → Sheet_A_Power_Refs.svg
    - Baseband PCB-Baseband_IF_Input_Protection_Bias.svg → Sheet_B_IF_Input.svg
    - Baseband PCB-Baseband_PGA_AntiAlias.svg → Sheet_C_PGA_Filter.svg
    - Baseband PCB-Baseband_FDA_Driver_ADC_SPI_Interface.svg → Sheet_D_FDA_ADC_SPI.svg
2026-03-28 Integrate KiCad schematic SVGs into System Design Document
    - Add .sch-wrap CSS class for white-background schematic containers
    - Add 'KiCad Schematics' sub-section to Table of Figures (6 entries)
    - Embed 6 SVGs via <img> in collapsible <details> wrappers:
    Fig 2.2c Root Hierarchy, Fig 3.1c Sheet A, Fig 4.1c Sheet B,
    Fig 5.1c Sheet C, Fig 5.4c Sheet C Annotated Audit, Fig 6.1c Sheet D
    - Sheet C annotated audit (Fig 5.4c) expanded by default
2026-03-28 Add filter analysis, system parameter chain, power/IO specs to SDD
    §2.4 Signal Budget replaced with cascaded system parameter chain:
    - Derivation chain from radar equation → ADC → filter → gain/bias
    - Chirp rate / sample rate / FFT coupling callout (Rev A vs Rev B)
    - Power supply rail specs: 5V input, 3V3A, 3V3D, VCM, VREF
    - Current budget: 12.8 mA typ / 17.5 mA max on 3V3A
    - I/O pin voltage specs for all analog, SPI, and reference pins
2026-03-28 Add §7 Layout Design Rationale, fix TOC, update README
    System Design Document:
    - §7 complete (6 subsections): stackup, placement, grounding,
    routing, DFT, manufacturing - all with first-principles derivations
    - Fix §7 TOC to use details/summary collapsible (matches §1-§6)
    - 5 new tables in §7
    - 2826 → 3159 lines
2026-03-29 Restructure SDD to TI datasheet format, update README
    SDD restructured from tutorial-style to TI datasheet conventions:
    1. Features (two-column specs at a glance)
    2. Applications
    3. Description
    4. Functional Block Diagram
    5. Pin Configuration and Functions
2026-03-29 Add schematic and PCB layout change plans to repo
    - Schematic_Updates_Change_Plan.docx: 9 CRs (SCH-00 through SCH-08)
    - PCB_Layout_Change_Plan.docx: 8 tasks (PCB-01 through PCB-08)
    - Fixes broken links in README.md
    - Force-added: *.docx is in .gitignore
2026-06-17 Reframe to 24 GHz FMCW radar system; restyle SDD to PMVB schema; resolve D1
2026-06-17 Reframe to 24 GHz FMCW radar system; restyle SDD to PMVB schema; resolve D1-D4
2026-06-17 README: link SDD to Rev B and trim Key Documents to the SDD
2026-06-17 Resolve D5 (calibrated DAC ramp); link SDD in README
2026-06-17 Resolve D6: chirp plan (250 MHz/1 ms, 50 m, 256 kSPS)
2026-06-17 Resolve D7: Tang Primer FPGA backend; D1-D7 complete
2026-06-17 SDD: add equations + figures, fix TOC links, add width slider, trim front matter
2026-06-17 Figures: TikZ + matplotlib pipeline; Section 5 references compiled figures
2026-06-17 Figures: full-width scaling; clean up chirp-beat labels
2026-06-17 Figure 5-1: two-panel multi-target chirp/beat diagram
2026-06-17 Figure 5-1: single-target two-panel, restore f_beat = S*tau and tau = 2R/c
